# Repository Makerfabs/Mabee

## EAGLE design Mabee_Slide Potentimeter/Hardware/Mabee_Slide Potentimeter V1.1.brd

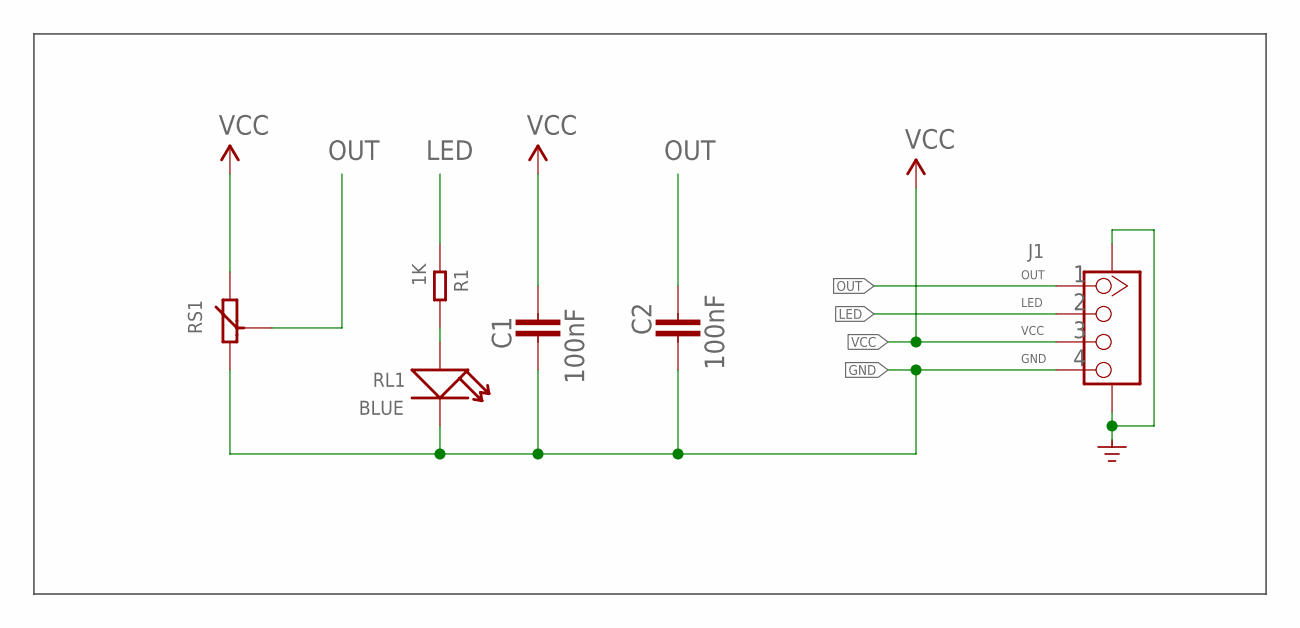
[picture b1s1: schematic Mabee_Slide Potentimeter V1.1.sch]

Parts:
C1, C2: 100nF; C0603
J1: GROVE-CONNECTOR-SMD'90D'; HW4-SMD-2.0-90D
R1: 1K; R0603
RL1: BLUE; LED-0603
RS1: R_SLIDE; R_SLIDE_DPT

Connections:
GND: C1.1, C2.1, J1.4, J1.SS1, J1.SS2, RL1.-, RS1.3
LED: J1.2, R1.1
unnamed: R1.2, RL1.+
OUT: C2.2, J1.1, RS1.2
VCC: C1.2, J1.3, RS1.1

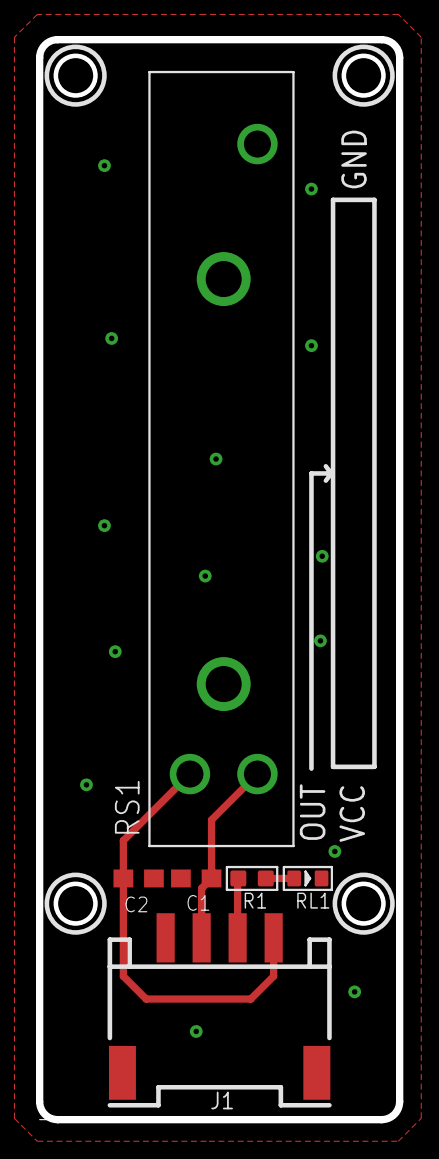
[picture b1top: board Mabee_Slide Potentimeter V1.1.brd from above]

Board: 2 copper layers, 20.0 x 60.0 mm, 7 parts (1 on the bottom side), 5 nets.

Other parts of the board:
U$2: MAKERFABS_0.3

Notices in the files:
parts and their libraries:
SparkFun-Aesthetics: Licensing: Creative Commons ShareAlike 4.0 International - https://creativecommons.org/licenses/by-sa/4.0
